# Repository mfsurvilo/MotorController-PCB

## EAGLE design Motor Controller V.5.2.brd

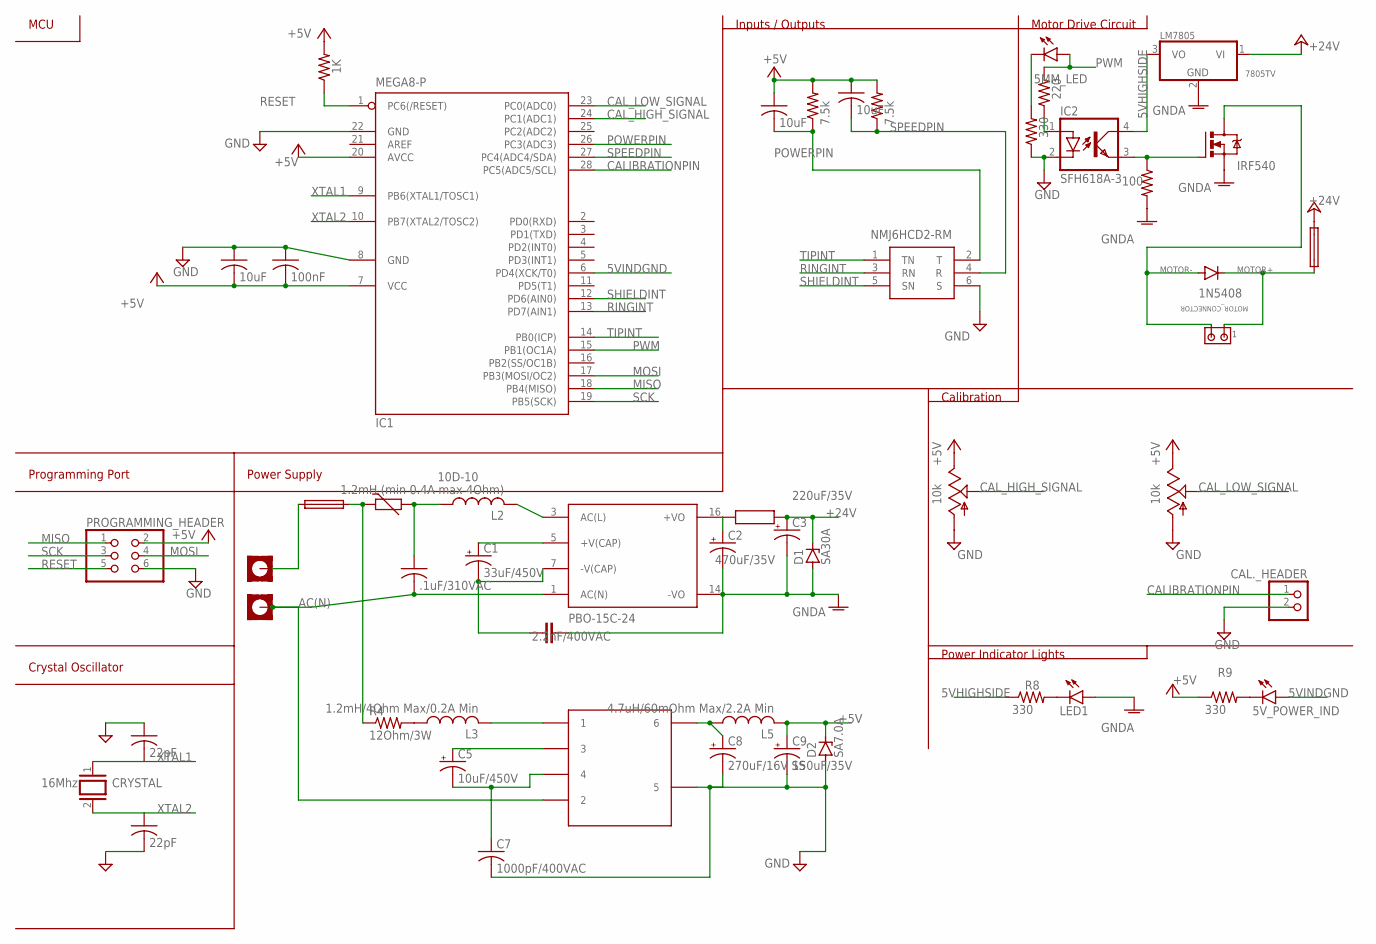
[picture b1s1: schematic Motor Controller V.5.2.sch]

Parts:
5V_POWER_IND: LED3MM
AC(N): PAD3.0; 3,0-PAD-SQUARE
C1: 33uF/450V; E5-13
C2: 470uF/35V; E5-10,5; MPN ECA1VHG471B
C3: 220uF/35V; E5-10,5; MPN A768KS227M1VLAE024
C4: .1uF/310VAC; C102-064X133
C5: 10uF/450V; E5-10,5
C6, C15: 22pF; C025-024X044
C7: 1000pF/400VAC; C075-052X106
C8: 270uF/16V SS; E2,5-6
C9: 150uF/35V; E3,5-8
C10, C12, C13: 10uF; C025-024X044
C14: 100nF; C025-024X044
CAL._HEADER: PINHD-1X2; 1X02
CRYSTAL: 16Mhz; QS
CY1: 2.2nF/400VAC; YC10B4
D1: SA30A; TVS-10
D2: SA7.0A; TVS-10
D3: 1N5408; DO201-15; MPN 1N5408-E3/54
F1: FUSESH22,5; SH22,5
F2: 1A/300V; SH22,5
FAST: 10k; CT6
H1: PAD3.0; 3,0-PAD-SQUARE
IC1: MEGA8-P; DIL28-3
IC2: SFH618A-3; DIP4
J1: NMJ6HCD2-RM; NMJ6HCD2RM
L2: 1.2mH (min 0.4A max 4Ohm); RCP1317_INDUCTOR
L3: 1.2mH/4Ohm Max/0.2A Min; RCP1317_INDUCTOR
L5: 4.7uH/60mOhm Max/2.2A Min; RLB0914_INDUCTOR
LED1: LED3MM
LM7805: 7805TV; TO220V
MOTOR_CONNECTOR: MATE-N-LOK_193839-1; MATE-N-LOK_2PIN_CONNECTOR
PROGRAMMING_HEADER: PINHD-2X3; 2X03
PS1: PBO-15C-24; CONV_PBO-15C-24
PWM_IND: 5MM_LED
Q1: IRF540; TO220BV
R1: 10D-10; R-7,5
R2: 1K; 0204/7
R3, R7: 7.5k; 0204/7
R4: 12Ohm/3W; VTA52
R5: 220; 0204/7
R6: 100; 0204/7
R8, R9, R10: 330; 0204/7
SLOW: 10k; CT6
U$1: L503-13B05R; LS03-13BO5R3
U$2: HCTI-22-16.4

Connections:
5VHIGHSIDE: IC2.4 (COL), LM7805.3 (VO), R8.1
5VINDGND: 5V_POWER_IND.A, IC1.6 (PD4(XCK/T0))
+5V: C9.+, C10.1, C12.1, C13.2, C14.2, D2.C, FAST.E, IC1.7 (VCC), IC1.20 (AVCC), L5.P$2 (2), PROGRAMMING_HEADER.2, R2.2, R3.2, R7.2, R9.1, SLOW.E
+24V: C3.+, D1.C, F1.2, LM7805.1 (VI), U$2.P$2
AC(L): L2.P$2 (2), PS1.3 (AC(L))
AC(N): AC(N).B3,0, C4.2, PS1.1 (AC(N)), U$1.3 (2), U$1.4 (2)
CALIBRATIONPIN: CAL._HEADER.1, IC1.28 (PC5(ADC5/SCL))
CAL_HIGH_SIGNAL: FAST.S, IC1.24 (PC1(ADC1))
CAL_LOW_SIGNAL: IC1.23 (PC0(ADC0)), SLOW.S
GND: C6.2, C7.2, C8.-, C9.-, C13.1, C14.1, C15.1, CAL._HEADER.2, D2.A, FAST.A, IC1.8 (GND), IC1.22 (GND), IC2.2 (C), J1.6 (S), PROGRAMMING_HEADER.6, R10.1, SLOW.A, U$1.9 (5), U$1.10 (5)
GNDA: C2.-, C3.-, CY1.1, D1.A, LED1.A, LM7805.2 (GND), PS1.14 (-VO), Q1.S, R6.2
MISO: IC1.18 (PB4(MISO)), PROGRAMMING_HEADER.1
MOSI: IC1.17 (PB3(MOSI/OC2)), PROGRAMMING_HEADER.4
MOTOR+: D3.C, F1.1, MOTOR_CONNECTOR.P$1 (1)
MOTOR-: D3.A, MOTOR_CONNECTOR.P$2 (2), Q1.D
unnamed: IC2.1 (A), R5.1
unnamed: IC2.3 (EMIT), Q1.G, R6.1
unnamed: LED1.K (C), R8.2
unnamed: C2.+, PS1.16 (+VO), U$2.P$1
unnamed: C1.+, PS1.5 (+V(CAP))
unnamed: C1.-, CY1.2, PS1.7 (-V(CAP))
unnamed: F2.2, H1.B3,0
unnamed: F2.1, R1.1, R4.1
unnamed: C4.1, L2.P$1 (1), R1.2
unnamed: 5V_POWER_IND.K (C), R9.2
unnamed: L3.P$1 (1), R4.2
unnamed: L3.P$2 (2), U$1.1, U$1.2 (1)
unnamed: C5.+, U$1.5 (3), U$1.6 (3)
unnamed: C5.-, C7.1, U$1.7 (4), U$1.8 (4)
unnamed: C8.+, L5.P$1 (1), U$1.11 (6), U$1.12 (6)
unnamed: PWM_IND.C, R10.2
POWERPIN: C10.2, IC1.26 (PC3(ADC3)), J1.2 (T), R3.1
PWM: IC1.15 (PB1(OC1A)), PWM_IND.A, R5.2
RESET: IC1.1 (PC6(/RESET)), PROGRAMMING_HEADER.5, R2.1
RINGINT: IC1.13 (PD7(AIN1)), J1.3 (RN)
SCK: IC1.19 (PB5(SCK)), PROGRAMMING_HEADER.3
SHIELDINT: IC1.12 (PD6(AIN0)), J1.5 (SN)
SPEEDPIN: C12.2, IC1.27 (PC4(ADC4/SDA)), J1.4 (R), R7.1
TIPINT: IC1.14 (PB0(ICP)), J1.1 (TN)
XTAL1: C15.2, CRYSTAL.1, IC1.9 (PB6(XTAL1/TOSC1))
XTAL2: C6.1, CRYSTAL.2, IC1.10 (PB7(XTAL2/TOSC2))

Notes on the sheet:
MCU
Motor Drive Circuit
Inputs / Outputs
Programming Port
Crystal Oscillator
Calibration
Power Supply
Power Indicator Lights

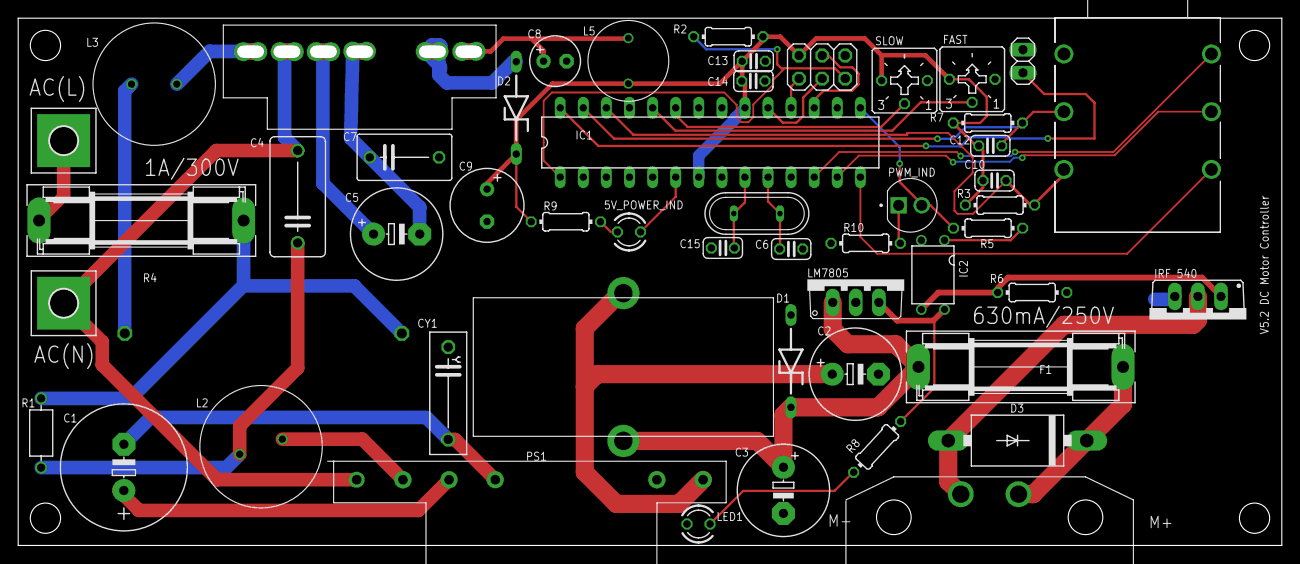
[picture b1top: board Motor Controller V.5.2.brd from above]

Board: 2 copper layers, 137.6 x 56.6 mm, 52 parts (1 on the bottom side), 41 nets.

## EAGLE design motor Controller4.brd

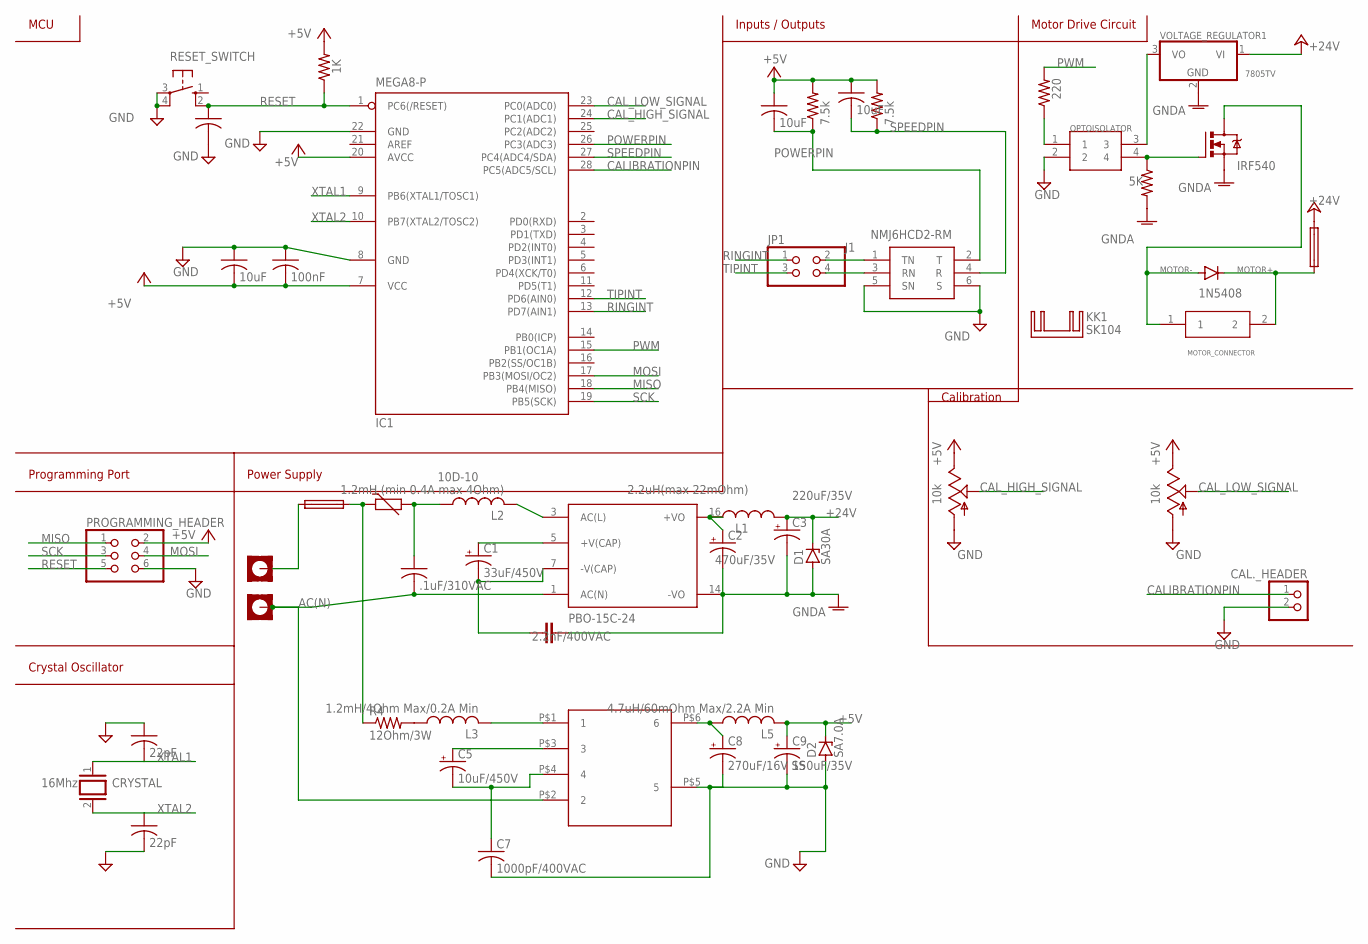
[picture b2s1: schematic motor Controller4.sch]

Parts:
1N5408: 1N5408; DO201-15; MPN 1N5408-E3/54
C1: 33uF/450V; E5-13
C2: 470uF/35V; E5-10,5; MPN ECA1VHG471B
C3: 220uF/35V; E5-10,5; MPN A768KS227M1VLAE024
C4: .1uF/310VAC; C150-091X182
C5: 10uF/450V; E5-10,5
C6, C15: 22pF; C025-024X044
C7: 1000pF/400VAC; C075-052X106
C8: 270uF/16V SS; E2,5-6
C9: 150uF/35V; E3,5-8
C10, C12, C13: 10uF; C025-024X044
C11: C-US025-024X044; C025-024X044
C14: 100nF; C025-024X044
CAL._HEADER: PINHD-1X2; 1X02
CRYSTAL: 16Mhz; QS
CY1: 2.2nF/400VAC; YC10B4
D1: SA30A; ZDIO-7.5
D2: SA7.0A; ZDIO-7.5
F1: FUSESH22,5; SH22,5
F2: 1A/300V; SH22,5
FAST: 10k; CT6
H1, H2: MOUNT-PAD-SQUARE3.6; 3,6-PAD-SQUARE
IC1: MEGA8-P; DIL28-3
J1: NMJ6HCD2-RM; NMJ6HCD2RM
JP1: PINHD-2X2; 2X02
KK1: SK104
L1: 2.2uH(max 22mOhm); TJ5-U1
L2: 1.2mH (min 0.4A max 4Ohm); 6000-XXXX-RC
L3: 1.2mH/4Ohm Max/0.2A Min; 6000-XXXX-RC
L5: 4.7uH/60mOhm Max/2.2A Min; 0207/2V
MOTOR_CONNECTOR: 641963-1; 641963-1_TYC
OPTOISOLATOR: SFH619A
PROGRAMMING_HEADER: PINHD-2X3; 2X03
PS1: PBO-15C-24; CONV_PBO-15C-24
Q1: IRF540; TO220BV
R1: 10D-10; R-7,5
R2: 1K; 0204/7
R3, R7: 7.5k; 0204/7
R4: 12Ohm/3W; 0617/22
R5: 220; 0204/7
R6: 5K; 0204/7
RESET_SWITCH: 10-XX; B3F-10XX
SLOW: 10k; CT6
U$1: L503-13B05R$3; LS03-13BO5R3
VOLTAGE_REGULATOR1: 7805TV; TO220V

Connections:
+5V: C9.+, C10.1, C12.1, C13.2, C14.2, D2.C, FAST.E, IC1.7 (VCC), IC1.20 (AVCC), L5.2, PROGRAMMING_HEADER.2, R2.2, R3.2, R7.2, SLOW.E
+24V: C3.+, D1.C, F1.2, L1.2, VOLTAGE_REGULATOR1.1 (VI)
AC(L): L2.2, PS1.3 (AC(L))
AC(N): C4.2, H2.B3,6, PS1.1 (AC(N)), U$1.P$2 (2)
CALIBRATIONPIN: CAL._HEADER.1, IC1.28 (PC5(ADC5/SCL))
CAL_HIGH_SIGNAL: FAST.S, IC1.24 (PC1(ADC1))
CAL_LOW_SIGNAL: IC1.23 (PC0(ADC0)), SLOW.S
GND: C6.2, C7.2, C8.-, C9.-, C11.2, C13.1, C14.1, C15.1, CAL._HEADER.2, D2.A, FAST.A, IC1.8 (GND), IC1.22 (GND), J1.5 (SN), J1.6 (S), OPTOISOLATOR.2, PROGRAMMING_HEADER.6, RESET_SWITCH.3, RESET_SWITCH.4 (P1), SLOW.A, U$1.P$5 (5)
GNDA: C2.-, C3.-, CY1.1, D1.A, PS1.14 (-VO), Q1.S, R6.2, VOLTAGE_REGULATOR1.2 (GND)
MISO: IC1.18 (PB4(MISO)), PROGRAMMING_HEADER.1
MOSI: IC1.17 (PB3(MOSI/OC2)), PROGRAMMING_HEADER.4
MOTOR+: 1N5408.C, F1.1, MOTOR_CONNECTOR.2
MOTOR-: 1N5408.A, MOTOR_CONNECTOR.1, Q1.D
unnamed: OPTOISOLATOR.1, R5.1
unnamed: OPTOISOLATOR.4, Q1.G, R6.1
unnamed: OPTOISOLATOR.3, VOLTAGE_REGULATOR1.3 (VO)
unnamed: C2.+, L1.1, PS1.16 (+VO)
unnamed: C1.+, PS1.5 (+V(CAP))
unnamed: C1.-, CY1.2, PS1.7 (-V(CAP))
unnamed: J1.1 (TN), JP1.2
unnamed: F2.2, H1.B3,6
unnamed: F2.1, R1.1, R4.1
unnamed: C4.1, L2.1, R1.2
unnamed: J1.3 (RN), JP1.4
unnamed: L3.1, R4.2
unnamed: L3.2, U$1.P$1 (1)
unnamed: C5.+, U$1.P$3 (3)
unnamed: C5.-, C7.1, U$1.P$4 (4)
unnamed: C8.+, L5.1, U$1.P$6 (6)
POWERPIN: C10.2, IC1.26 (PC3(ADC3)), J1.2 (T), R3.1
PWM: IC1.15 (PB1(OC1A)), R5.2
RESET: C11.1, IC1.1 (PC6(/RESET)), PROGRAMMING_HEADER.5, R2.1, RESET_SWITCH.2 (S1)
RINGINT: IC1.13 (PD7(AIN1)), JP1.1
SCK: IC1.19 (PB5(SCK)), PROGRAMMING_HEADER.3
SPEEDPIN: C12.2, IC1.27 (PC4(ADC4/SDA)), J1.4 (R), R7.1
TIPINT: IC1.12 (PD6(AIN0)), JP1.3
XTAL1: C15.2, CRYSTAL.1, IC1.9 (PB6(XTAL1/TOSC1))
XTAL2: C6.1, CRYSTAL.2, IC1.10 (PB7(XTAL2/TOSC2))

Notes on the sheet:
MCU
Motor Drive Circuit
Inputs / Outputs
Programming Port
Crystal Oscillator
Calibration
Power Supply

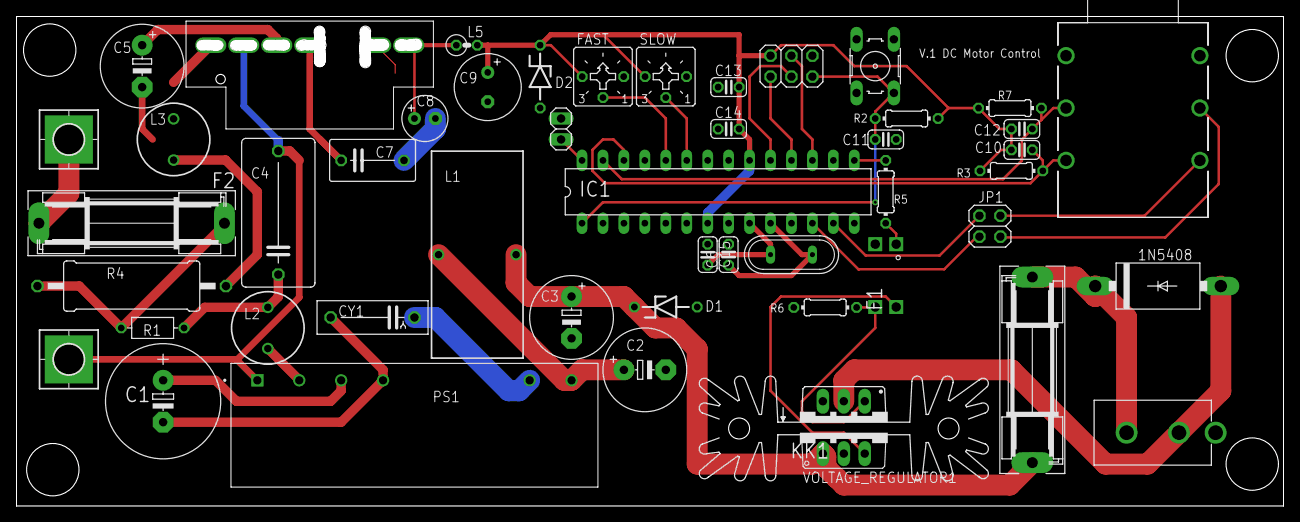
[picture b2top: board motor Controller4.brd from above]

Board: 2 copper layers, 152.5 x 58.2 mm, 50 parts (0 on the bottom side), 38 nets.

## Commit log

2021-07-21 Ver.5 Prep for second print
2021-07-21 Ver.5 All files added
2021-07-24 Starting to route on new board with updated components. v5.1
2021-07-24 Start routing on new board with updated components v5.1
2021-08-20 Add ver 5.2 board design
